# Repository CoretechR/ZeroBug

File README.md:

# ZeroBug - DIY Hexapod Robot

Zerobug is a 3D-printed micro-servo hexapod robot powered by a Raspberry Pi Zero and a STM32F103. The Pi Zero is in charge of the input methods and front end, making the robot controllable via mouse, keyboard, multitouch or simply a Bluetooth Gamepad. To get the robot walking, the STM32 handles leg locomotion, inverse kinematics and controls its 18 servos.

UPDATE 20.11.2021: Added support for video streaming with via the camera connector:
 - update the index-html file and copy "start_stream.sh" to the same directory on the desktop
 - install mjpg-streamer (e.g. using this guide: https://www.okdo.com/project/pc-webcam-with-raspberry-pi/?ok_ts=1635608250445)
 - add the following line to the /etc/rc.local file (before exit 0):
```
bash /home/pi/Desktop/hexapod/start_stream.sh
```

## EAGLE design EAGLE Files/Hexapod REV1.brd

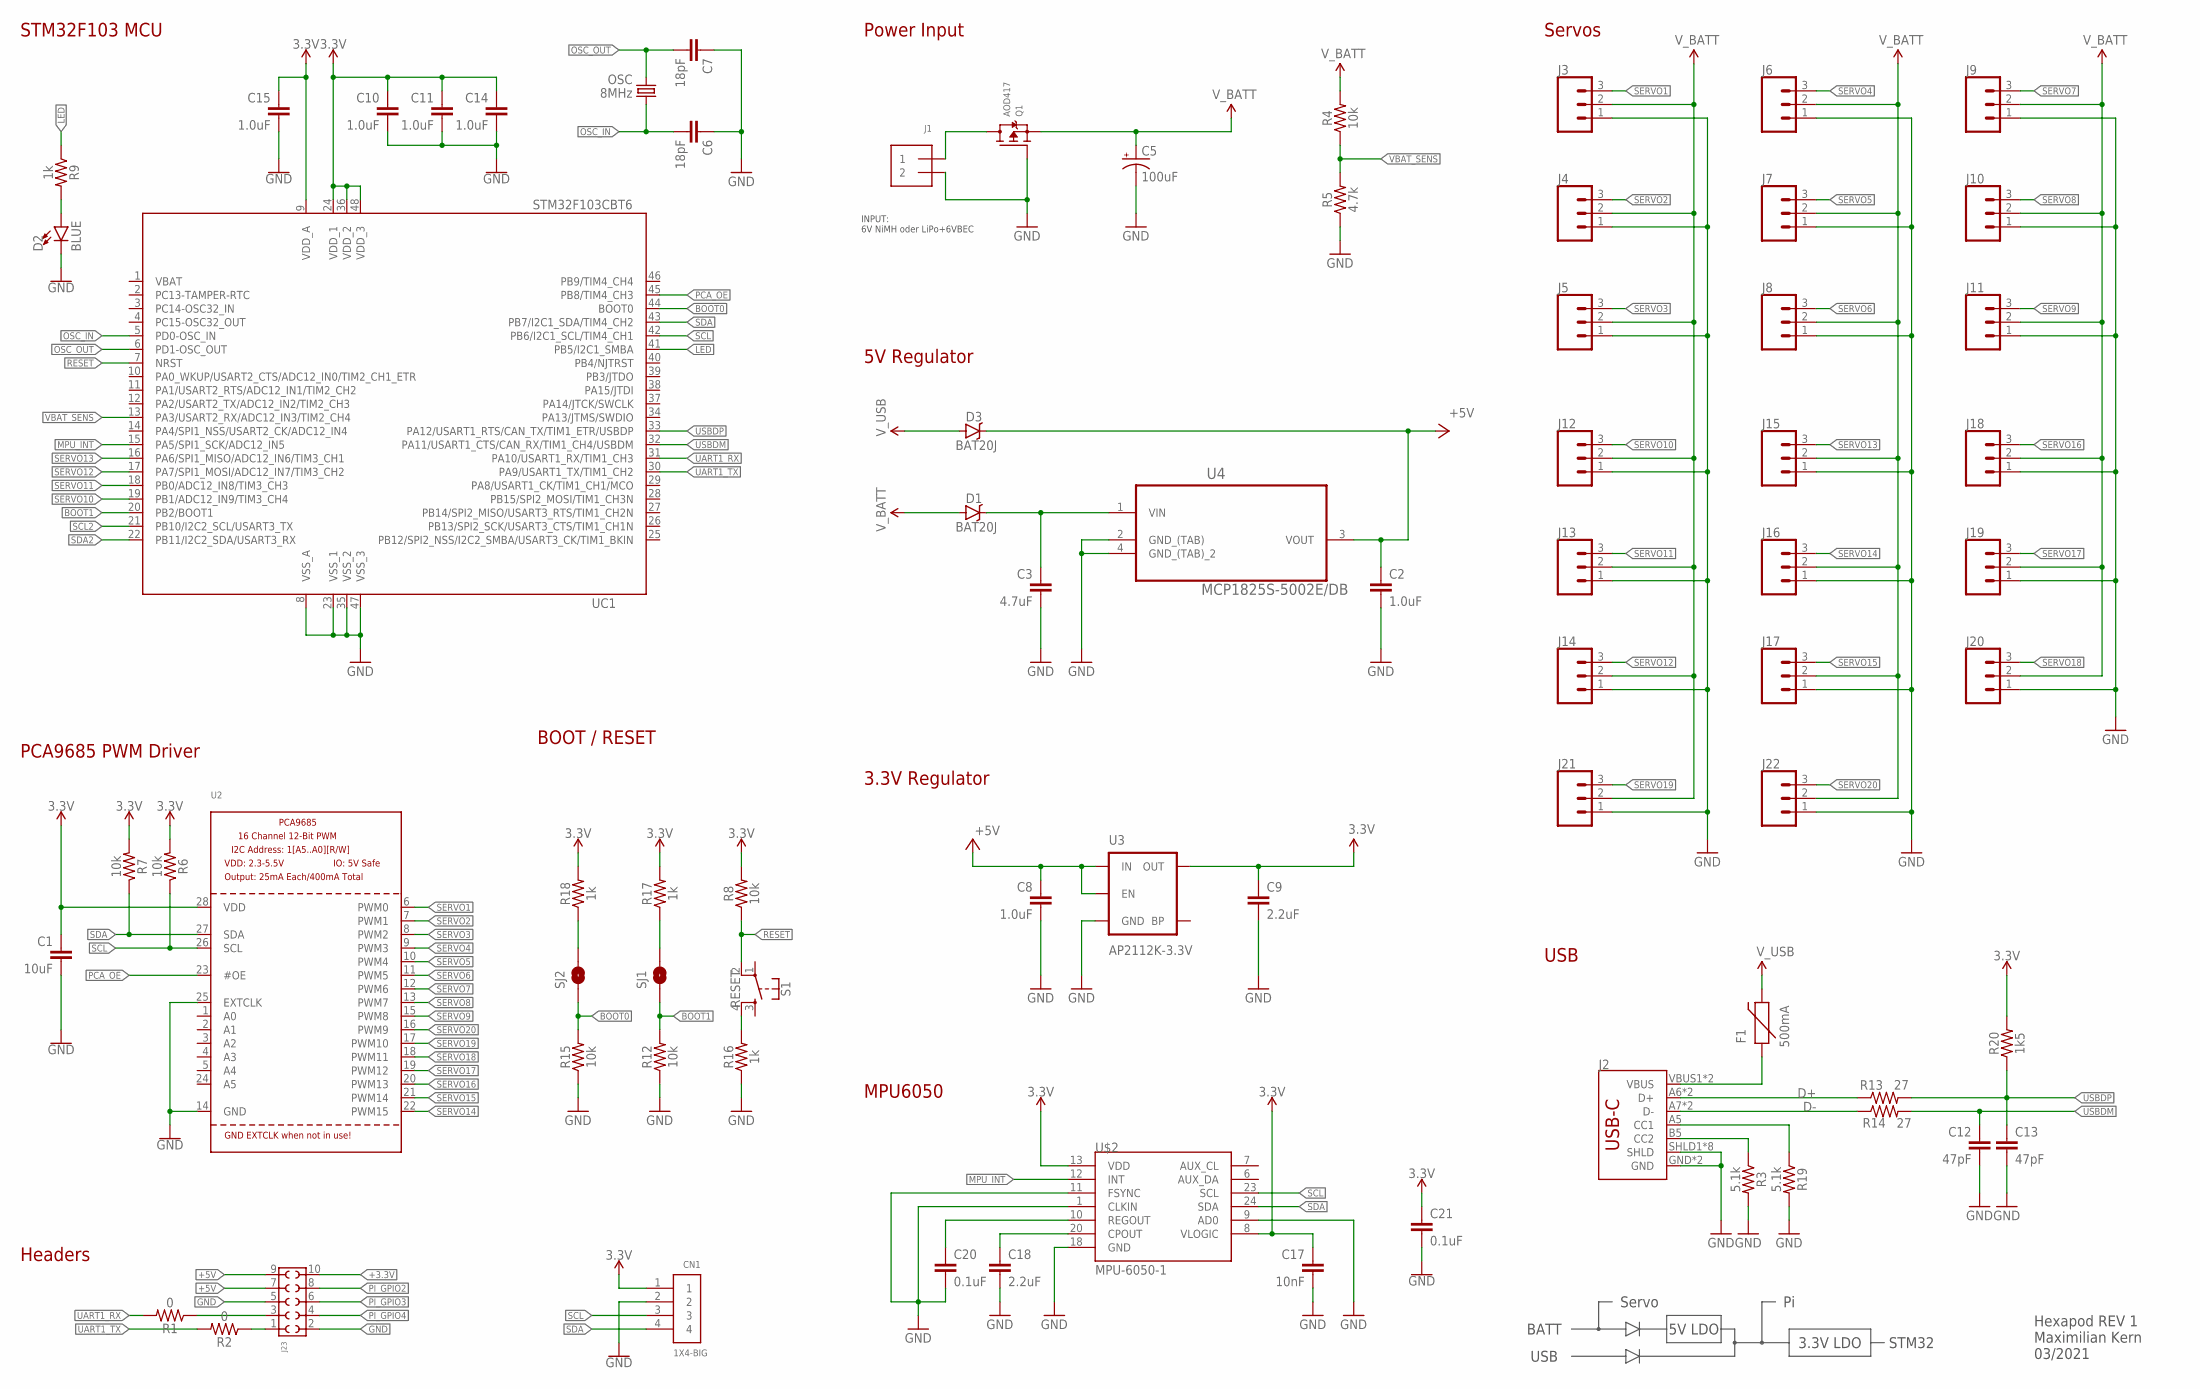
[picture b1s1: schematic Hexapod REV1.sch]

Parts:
C1: 10uF; 0805
C2, C8, C10, C11, C14, C15: 1.0uF; 0805
C3: 4.7uF; 0805
C5: 100uF; PANASONIC_D
C6, C7: 18pF; 0603
C9, C18: 2.2uF; 0805
C12, C13: 47pF; 0603
C17: 10nF; 0603
C20, C21: 0.1uF; 0603
CN1: 1X4-BIG; 1X04-BIG
D1, D3: BAT20J; SOD-323
D2: BLUE; LED-0603@2
F1: 500mA; PTC-1206
J1: TERMBLOCK_1X2; TERMBLOCK_1X2-3.5MM
J2: USB_C16PIN; USB-C-16P
J3, J4, J5, J6, J7, J8, J9, J10, J11, J12, J13, J14, J15, J16, J17, J18, J19, J20, J21, J22: CONN_03; 1X03
J23: 6103XX21821_61031021821; 61031021821
OSC: 8MHz; CRYSTAL-SMD-5X3
Q1: AOD417; TO252
R1, R2: 0; 0603
R3, R19: 5.1k; 0603
R4, R6, R7, R8, R12, R15: 10k; 0603
R5: 4.7k; 0603
R9, R16, R17, R18: 1k; 0603
R13, R14: 27; 0603
R20: 1k5; 0603
S1: RESET; TACTILE_SWITCH_SMD_4.6X2.8MM
SJ1, SJ2: JUMPER-PAD-2-NOYES_SILK; PAD-JUMPER-2-NO_YES_SILK
U2: PCA9685; TSSOP28
U3: AP2112K-3.3V; SOT23-5
U4: MCP1825S-5002E/DB; SOT230P700X180-4N
U$2: MPU-6050-1; QFN-24-4MM2
UC1: STM32F103CBT6; LQFP48

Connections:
3.3V: C1.1, C9.1, C10.1, C11.1, C14.1, C15.1, C17.1, C21.1, CN1.1, R6.2, R7.2, R8.2, R17.2, R18.2, R20.2, U2.28 (VDD), U3.5 (OUT), U$2.8 (VLOGIC), U$2.13 (VDD), UC1.9 (VDD_A), UC1.24 (VDD_1), UC1.36 (VDD_2), UC1.48 (VDD_3)
+3.3V: J23.10
+5V: C2.1, C8.1, D3.C, J23.7, J23.9, U3.1 (IN), U3.3 (EN), U4.3 (VOUT)
BOOT0: R15.2, SJ2.1, UC1.44 (BOOT0)
BOOT1: R12.2, SJ1.1, UC1.20 (PB2/BOOT1)
D+: J2.A6 (D+), J2.B6 (D+), R13.1
D-: J2.A7 (D-), J2.B7 (D-), R14.1
GND: C1.2, C2.2, C3.2, C5.-, C6.1, C7.1, C8.2, C9.2, C10.2, C11.2, C12.2, C13.2, C14.2, C15.2, C17.2, C18.2, C20.2, C21.2, CN1.2, D2.C, J1.2, J2.GND, J2.GND2 (GND), J2.SHLD1 (SHLD), J2.SHLD2 (SHLD), J2.SHLD3 (SHLD), J2.SHLD4 (SHLD), J2.SHLD5 (SHLD), J2.SHLD6 (SHLD), J2.SHLD7 (SHLD), J2.SHLD8 (SHLD), J3.1, J4.1, J5.1, J6.1, J7.1, J8.1, J9.1, J10.1, J11.1, J12.1, J13.1, J14.1, J15.1, J16.1, J17.1, J18.1, J19.1, J20.1, J21.1, J22.1, J23.2, J23.5, Q1.1 (G), R3.2, R5.1, R12.1, R15.1, R16.1, R19.2, U2.14 (GND), U2.25 (EXTCLK), U3.2 (GND), U4.2 (GND_(TAB)), U4.4 (GND_(TAB)_2), U$2.1 (CLKIN), U$2.9 (AD0), U$2.11 (FSYNC), U$2.18 (GND), UC1.8 (VSS_A), UC1.23 (VSS_1), UC1.35 (VSS_2), UC1.47 (VSS_3)
LED: R9.1, UC1.41 (PB5/I2C1_SMBA)
MPU_INT: U$2.12 (INT), UC1.15 (PA5/SPI1_SCK/ADC12_IN5)
unnamed: R16.2, S1.4
unnamed: R18.1, SJ2.2
unnamed: R17.1, SJ1.2
unnamed: C3.1, D1.C, U4.1 (VIN)
unnamed: D2.A, R9.2
unnamed: J1.1, Q1.3 (D)
unnamed: J2.A5 (CC1), R19.1
unnamed: J2.B5 (CC2), R3.1
unnamed: C18.1, U$2.20 (CPOUT)
unnamed: C20.1, U$2.10 (REGOUT)
OSC_IN: C6.2, OSC.1, UC1.5 (PD0-OSC_IN)
OSC_OUT: C7.2, OSC.3 (2), UC1.6 (PD1-OSC_OUT)
PCA_OE: U2.23 (#OE), UC1.45 (PB8/TIM4_CH3)
PI_GPIO2: J23.8
PI_GPIO3: J23.6
PI_GPIO4: J23.4
PI_RXD: J23.1, R2.1
PI_TXD: J23.3, R1.1
RESET: R8.1, S1.2, UC1.7 (NRST)
SCL: CN1.3, R6.1, U2.26 (SCL), U$2.23 (SCL), UC1.42 (PB6/I2C1_SCL/TIM4_CH1)
SCL2: UC1.21 (PB10/I2C2_SCL/USART3_TX)
SDA: CN1.4, R7.1, U2.27 (SDA), U$2.24 (SDA), UC1.43 (PB7/I2C1_SDA/TIM4_CH2)
SDA2: UC1.22 (PB11/I2C2_SDA/USART3_RX)
SERVO1: J3.3, U2.6 (PWM0)
SERVO2: J4.3, U2.7 (PWM1)
SERVO3: J5.3, U2.8 (PWM2)
SERVO4: J6.3, U2.9 (PWM3)
SERVO5: J7.3, U2.10 (PWM4)
SERVO6: J8.3, U2.11 (PWM5)
SERVO7: J9.3, U2.12 (PWM6)
SERVO8: J10.3, U2.13 (PWM7)
SERVO9: J11.3, U2.15 (PWM8)
SERVO10: J12.3, UC1.19 (PB1/ADC12_IN9/TIM3_CH4)
SERVO11: J13.3, UC1.18 (PB0/ADC12_IN8/TIM3_CH3)
SERVO12: J14.3, UC1.17 (PA7/SPI1_MOSI/ADC12_IN7/TIM3_CH2)
SERVO13: J15.3, UC1.16 (PA6/SPI1_MISO/ADC12_IN6/TIM3_CH1)
SERVO14: J16.3, U2.22 (PWM15)
SERVO15: J17.3, U2.21 (PWM14)
SERVO16: J18.3, U2.20 (PWM13)
SERVO17: J19.3, U2.19 (PWM12)
SERVO18: J20.3, U2.18 (PWM11)
SERVO19: J21.3, U2.17 (PWM10)
SERVO20: J22.3, U2.16 (PWM9)
UART1_RX: R1.2, UC1.31 (PA10/USART1_RX/TIM1_CH3)
UART1_TX: R2.2, UC1.30 (PA9/USART1_TX/TIM1_CH2)
USBDM: C12.1, R14.2, UC1.32 (PA11/USART1_CTS/CAN_RX/TIM1_CH4/USBDM)
USBDP: C13.1, R13.2, R20.1, UC1.33 (PA12/USART1_RTS/CAN_TX/TIM1_ETR/USBDP)
VBAT: UC1.1 (VBAT)
VBAT_SENS: R4.1, R5.2, UC1.13 (PA3/USART2_RX/ADC12_IN3/TIM2_CH4)
VUSB-RAW: F1.1, J2.VBUS1 (VBUS), J2.VBUS2 (VBUS)
V_BATT: C5.+, D1.A, J3.2, J4.2, J5.2, J6.2, J7.2, J8.2, J9.2, J10.2, J11.2, J12.2, J13.2, J14.2, J15.2, J16.2, J17.2, J18.2, J19.2, J20.2, J21.2, J22.2, Q1.2 (S), R4.2
V_USB: D3.A, F1.2

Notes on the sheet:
STM32F103 MCU
USB
BOOT / RESET
3.3V Regulator
Hexapod REV 1 Maximilian Kern 03/2021
INPUT: 6V NiMH oder LiPo+6VBEC
5V LDO
3.3V LDO
Servo
BATT
STM32
MPU6050
Power Input
Servos
PCA9685 PWM Driver
Headers
5V Regulator

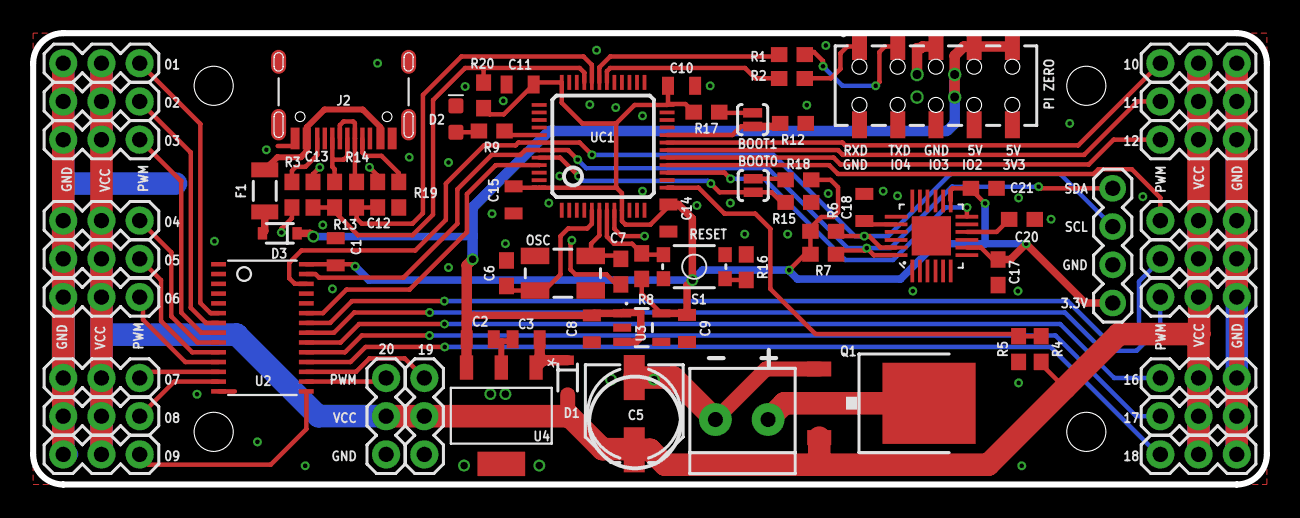
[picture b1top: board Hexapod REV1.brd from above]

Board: 2 copper layers, 82.0 x 30.0 mm, 74 parts (0 on the bottom side), 55 nets.

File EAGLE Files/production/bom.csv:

Designator,Footprint,Quantity,Value,LCSC Part #
"@HOLE0, @HOLE1, @HOLE10, @HOLE11, @HOLE12, @HOLE13, @HOLE2, @HOLE3, @HOLE4, @HOLE5, @HOLE6, @HOLE7, @HOLE8, @HOLE9",,14,,
C1,0805,1,10uF,
"C10, C11, C14, C15, C2, C8",0805,6,1.0uF,
"C12, C13",0603,2,47pF,
C17,0603,1,10nF,
"C18, C9",0805,2,2.2uF,
"C20, C21",0603,2,0.1uF,
C3,0805,1,4.7uF,
C5,PANASONIC_D,1,100uF,
"C6, C7",0603,2,18pF,
CN1,1X04-BIG,1,1X4-BIG,
"D1, D3",SOD-323,2,BAT20J,
D2,LED-0603@2,1,BLUE,
F1,PTC-1206,1,500mA,
J1,TERMBLOCK_1X2-3.5MM,1,,
"J10, J11, J12, J13, J14, J15, J16, J17, J18, J19, J20, J21, J22, J3, J4, J5, J6, J7, J8, J9",1X03,20,,
J2,USB-C-16P,1,,
J23,61031021821,1,,
OSC0,CRYSTAL-SMD-5X3,1,8MHz,
Q1,TO252,1,AOD417,
"R1, R2",0603,2,0,
"R12, R15, R4, R6, R7, R8",0603,6,10k,
"R13, R14",0603,2,27,
"R16, R17, R18, R9",0603,4,1k,
"R19, R3",0603,2,5.1k,
R20,0603,1,1k5,
R5,0603,1,4.7k,
S1,TACTILE_SWITCH_SMD_4.6X2.8MM,1,RESET,
"SJ1, SJ2",PAD-JUMPER-2-NO_YES_SILK,2,,
U$2,QFN-24-4MM2,1,MPU-6050-1,
U2,TSSOP28,1,,
U3,SOT23-5,1,AP2112K-3.3V,
U4,SOT230P700X180-4N,1,MCP1825S-5002E/DB,
UC1,LQFP48,1,STM32F103CBT6,

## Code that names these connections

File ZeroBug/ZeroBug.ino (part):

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#include <Adafruit_PWMServoDriver.h>
#include <Servo.h>

#define LED PB5
#define SDA1 PB7
#define SCL1 PB6
#define PCA_OE PB8

Adafruit_PWMServoDriver pwm = Adafruit_PWMServoDriver(0x40, Wire);

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void setup() {

  pinMode(LED, OUTPUT);
  pinMode(PCA_OE, OUTPUT);  
  digitalWrite(PCA_OE, HIGH);
  
  // tripod gait
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  static int testVal = SERVOMIN;
  if(testVal >= SERVOMAX) testVal = SERVOMIN;

  vBat = (float(analogRead(PA3))/4069.0)*10.321; // 4.7K+10K voltage divider

  batteryCheck();
    
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  static boolean servosEnabled = false;
  if(!servosEnabled && servOn){
    digitalWrite(PCA_OE, LOW);
    servo[0].attach(PB1, SERVOMIN, SERVOMAX);
    servo[1].attach(PB0, SERVOMIN, SERVOMAX);
    servo[2].attach(PA7, SERVOMIN, SERVOMAX);
    servo[3].attach(PA6, SERVOMIN, SERVOMAX);
    servosEnabled = true;
  }
  else if(servosEnabled && !servOn){
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
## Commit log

2021-06-30 Stopped the robot from moving by itself
2021-08-12 Fixed include error
2021-08-18 BOM added
2021-11-20 Camera Streaming
    added support for displaying a video stream in the web-UI
2021-11-20 Added instructions for video streaming
2024-06-13 production files added

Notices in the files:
parts and their libraries:
SparkFun-Capacitors: Licensing: Creative Commons ShareAlike 4.0 International - https://creativecommons.org/licenses/by-sa/4.0
Eagle_WR-PHD: Copyright: Würth Elektronik
